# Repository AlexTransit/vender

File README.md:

# What
Vender is free open source VMC (Vending Machine Controller). (fork https://github.com/temoto/vender)
This software has been working since 2019 (small network of coffee machines.)
equipment used:
VMC: eVend8 (bill validators: JCM300 and ICT7, Coin validators: CoinCo Global2 and Coges Aeterna)
Main Board: OrangePi Lite, 
additional display: 320x240 controller st7789v 
additional sound card: noname USB sound card

Status:
- MDB adapter hardware module - works
- VMC - works

# Hardware

Required for VMC:
- Works on RaspberryPI, OrangePi Lite (H3) OrangePi PC2(H5). Possibly anything with GPIO that runs Go/Linux.
- MDB signal current limiter - required, see files in `hardware/schematic` (https://namanow.org/wp-content/uploads/Multi-Drop-Bus-and-Internal-Communication-Protocol.pdf)
- MDB adapter, takes care of 9bit and timing, we use ATMega328p (168) with `hardware/mega-firmware`. 
    (software option is available: https://github.com/temoto/iodin . in a similar solution, another author made measurements. delay may be up to 10ms. in the specification MDB the maximum delay is 5ms )

Supported peripherals:
- MDB coin acceptor, bill validator
- Evend MDB drink devices
- any MDB device via configuration scenarios (work in progress)
- MT16S2R HD44780-like text display
- TWI(I2C) numpad keyboard
- graphic display (anyone registered in the system.)

# Design

VMC overall structure:
- engine (see internal/engine packages) executes actions, handles concurrency and errors
- device/feature drivers provide actions to engine
- configuration scenario specifies action groups and when to execute them

# Build

- Install latest Go from https://golang.org/dl/ (now worked on 1.24)
- Set target environment, default is `GOARCH=arm GOOS=linux`
- Run `script/build`
- Deploy file `build/vender` to your hardware

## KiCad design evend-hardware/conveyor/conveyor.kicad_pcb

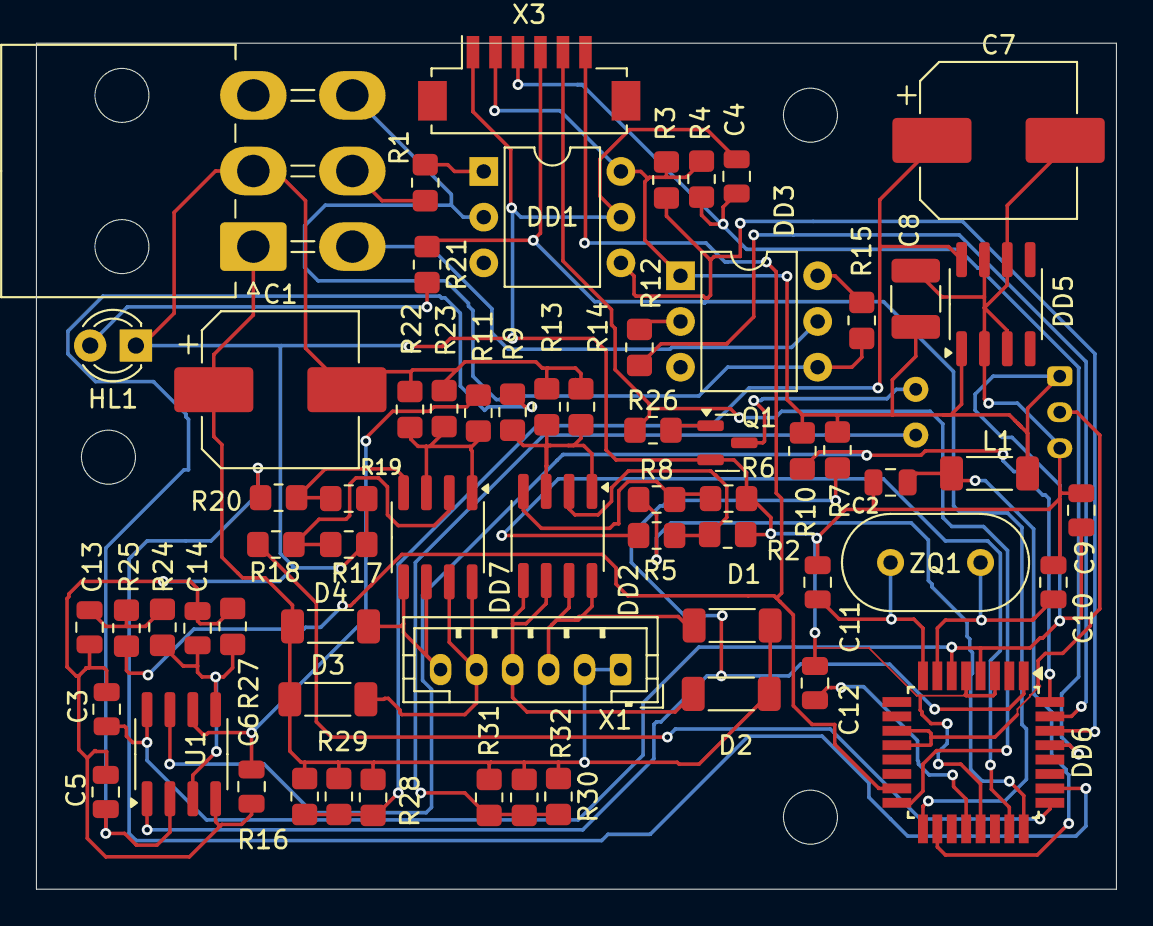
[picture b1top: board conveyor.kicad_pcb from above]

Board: 2 copper layers, 60.0 x 47.0 mm, 65 parts (1 on the bottom side), 45 nets.

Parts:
C1, C7: 100 35v; CP_Elec_8x10.5
C2, C3, C4, C5, C6, C9, C10, C11, C12, C13, C14: C; C_0805_2012Metric
C8: TAN; C_1210_3225Metric_Pad1.33x2.70mm_HandSolder
D1, D2, D3, D4: 10BQ060; L_1806_4516Metric
DD1: H11L1; DIP-6_W7.62mm
DD2, DD7: F7341; SOIC-8_3.9x4.9mm_P1.27mm
DD3: 4N37; DIP-6_W7.62mm
DD5: L78L05_SO8; SOIC-8_3.9x4.9mm_P1.27mm
DD6: ATmega8-16A; TQFP-32_7x7mm_P0.8mm
HL1: LED; LED_D3.0mm
L1: L; L_1806_4516Metric
Q1: Q_NPN_BEC; SOT-23
R1: 152; R_0805_2012Metric_Pad1.20x1.40mm_HandSolder
R2, R6, R17, R19, R25: 513; R_0805_2012Metric_Pad1.20x1.40mm_HandSolder
R3, R7, R10, R26, R30, R31, R32: 472; R_0805_2012Metric_Pad1.20x1.40mm_HandSolder
R4, R9, R11, R27: 103; R_0805_2012Metric_Pad1.20x1.40mm_HandSolder
R5, R8, R12, R18, R20: 181; R_0805_2012Metric_Pad1.20x1.40mm_HandSolder
R13, R14, R22, R23: 1; R_0805_2012Metric_Pad1.20x1.40mm_HandSolder
R15: 104; R_0805_2012Metric_Pad1.20x1.40mm_HandSolder
R16, R28, R29: 122; R_0805_2012Metric_Pad1.20x1.40mm_HandSolder
R21: 102; R_0805_2012Metric_Pad1.20x1.40mm_HandSolder
R24: 363; R_0805_2012Metric_Pad1.20x1.40mm_HandSolder
U1: LM393; SOIC-8_3.9x4.9mm_P1.27mm
US1: LG206D; Kodenshi_LG206D
X1: Conn_01x06; JST_PH_B6B-PH-K_1x06_P2.00mm_Vertical
X2: MDB; Molex_Mini-Fit_Jr_5569-06A2_2x03_P4.20mm_Horizontal
X3: Conn_01x06; Hirose_DF13C_CL535-0406-3-51_1x06-1MP_P1.25mm_Vertical
ZQ1: 7.3728; Resonator-2Pin_W10.0mm_H5.0mm

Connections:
+5V: C3.2, C8.1, C9.2, DD1.6, DD3.1, DD5.1 (OUT), DD6.4 (VCC), DD6.6 (VCC), L1.1, R3.1, R4.2, R7.1, R10.1, U1.8 (V+), US1.1 (VCC), X3.2
+24V: C1.1, D1.1 (K), D2.1 (K), D3.1 (K), D4.1 (K), R16.1, R28.1, R29.1, R30.1, R31.1, R32.1, X1.1, X1.2, X2.1
GND: C1.2, C2.1, C3.1, C4.2, C5.1, C6.1, C7.2, C8.2, C9.1, C10.1, C11.1, C12.1, C13.1, C14.1, DD1.5, DD5.2 (GND), DD5.3 (GND), DD5.6 (GND), DD5.7 (GND), DD6.3 (GND), DD6.5 (GND), DD6.21 (AGND), HL1.1 (K), Q1.2 (E), R2.2, R6.2, R13.2, R14.2, R17.2, R19.2, R22.2, R23.2, R27.1, U1.4 (V-), US1.3 (GND), X2.2, X3.1
GNDS: DD1.2, DD3.4, R15.1, X2.6
unnamed: C13.2, R24.1, R25.2
unnamed: DD1.1, R1.2
unnamed: DD2.2 (G), R2.1, R5.2
unnamed: DD2.1 (S), DD2.3 (1), R9.1, R13.1, R14.1
unnamed: DD2.4 (G), R6.1, R8.2
unnamed: DD3.2, R12.2
unnamed: DD3.6, R15.2
unnamed: C7.1, DD5.8 (IN), R16.2, R28.2, R29.2
unnamed: C12.2, DD6.20 (AREF)
unnamed: C2.2, DD6.18 (AVCC), L1.2
unnamed: C10.2, DD6.7 (PB6/XTAL1), ZQ1.1
unnamed: C11.2, DD6.8 (PB7/XTAL2), ZQ1.2
unnamed: DD7.2 (G), R17.1, R18.2
unnamed: DD7.1 (S), DD7.3 (1), R11.1, R22.1, R23.1
unnamed: DD7.4 (G), R19.1, R20.2
unnamed: HL1.2 (A), R21.2
unnamed: Q1.1 (B), R26.2
unnamed: Q1.3 (C), US1.5 (K)
unnamed: C14.2, R25.1, R27.2, U1.3 (+), U1.5 (+)
unnamed: C5.2, R9.2, U1.2 (-)
unnamed: C6.2, R11.2, U1.6 (-)
unnamed: R30.2, R31.2, R32.2, US1.4 (A)
unnamed: DD3.5, X2.4
unnamed: R1.1, X2.5
RX: DD1.4, DD6.30 (PD0), R3.2
TX: DD6.31 (PD1), R12.1
c-w11: DD6.23 (PC0), R5.1
c-w12: DD6.24 (PC1), R8.1
c-w21: DD6.25 (PC2), R18.1
c-w22: DD6.26 (PC3), R20.1
cc1: DD6.1 (PD3), R7.2, U1.1
cc2: DD6.32 (PD2), R10.2, U1.7
encoder: DD6.11 (PD7), DD6.12 (PB0), US1.2 (VOUT)
miso: DD6.16 (PB4), R26.1, X3.5
mosi: DD6.15 (PB3), R24.2, X3.6
reset: C4.1, DD6.29 (PC6/~RESET), R4.1, X3.3
sck: DD6.17 (PB5), R21.1, X3.4
winding1-1: D1.2 (A), DD2.7 (D), DD2.8 (D), X1.3
winding1-2: D2.2 (A), DD2.5 (D), DD2.6 (D), X1.4
winding2-1: D3.2 (A), DD7.7 (D), DD7.8 (D), X1.5
winding2-2: D4.2 (A), DD7.5 (D), DD7.6 (D), X1.6

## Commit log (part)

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2024-02-07 add device error code
2024-02-07 elevator rewirite
2024-02-09 config rewrite
2024-02-10 override structure. add function
2024-02-10 add config hardware override
2024-02-13 upgrade go 1.22
2024-02-24 dev set errorcode proto2
2024-02-24 espresso grind restart
2024-02-25 mon. remove gift? change dispence
2024-02-25 modify coin dispense
2024-02-26 fix coges bug. (diagnostics return )
2024-03-02 -- fix warning
2024-03-02 coin. add return and status
2024-03-02 sound volume fix
2024-03-04 wd disabled fix
2024-03-04 esspresso grind 5 times
2024-03-12 espresso grind
2024-03-12 valve remove hot validate
2024-03-12 valve
2024-04-12 mix err
2024-05-02 tune key
2024-05-14 change valve timeout pool
2024-05-14 fix water run timeout
2024-06-09 change input init
2024-06-10 set arg as interface
2024-06-10 added text in scenario
2024-06-10 added sound play in scenario
2024-07-27 added autosync atribute on inventoryf ile
2024-07-30 set atribute via unix package
2024-10-23 add conveyor plate shematic
2024-11-15 inventory. changing file handling
2024-12-06 fix. qr cancel
2024-12-07 upgrade protobuf lib
2024-12-07 upgrade protobuff
2024-12-08 add payer order amount in show qr proto
2024-12-08 переделал commang.go
2024-12-08 fix 2 bugs
2024-12-09 automatically sets the service button
2024-12-10 add check menu and --
2024-12-10 fix. restore stty after engine-cli
2024-12-21 отделил меню
2024-12-28 default config
2025-01-12 auto level-value in service
2025-01-13 broken file to config
2025-01-15 upgrade go 1,23.4
2025-01-16 auto reporter
2025-01-16 end work state
2025-01-17 fix QR amount
2025-01-20 calc cost
2025-01-20 fix text lines (qr)
2025-01-20 fix deprecated
2025-01-20 fix. remove test string
2025-01-20 fix bug
2025-01-21 espresso. grind func for stok
2025-01-21 stop money pull if money abort/
2025-01-29 show coins when loading
2025-03-30 fix bill stop
2025-03-31 fix bill escrow
2025-04-02 fix bill stop. reject escow
2025-04-05 set coplete order if dirty 0
2025-04-16 mixer add restart if shake
2025-04-17 uggrade sound add tts
2025-05-18 update conveyor schematic
2025-05-28 optimize structs
2025-05-31 dispence max amount if count =
2025-05-31 Revert "optimize structs"
    This reverts commit dccf9ed9d7241209e4a64344aeacbecc6a1394d0.
2025-06-08 bill bancnote limit
2025-07-10 upgrade mqtt
2025-07-10 fix mqtt panic
2025-07-11 fix mix timiout error
2025-08-16 remove unused
2025-08-17 fix nil doer on remote cook
2025-08-17 fix fix
2025-09-04 show mix gopp action
2025-09-07 fix syntax
2025-10-11 fix make tuned selected cook
2025-10-16 set custom charmap
2025-10-16 страницы знакогенераторов на экранах 1602 уже не используются.
2026-02-07 update mqtt
2026-02-07 add makefile
2026-02-10 fix sound
2026-02-10 update sound lib
2026-02-12 update makefile and settings
2026-02-12 fix makefile
2026-02-20 update tele (add webuser
2026-03-03 update make
2026-03-06 remote cook. check overdraft
2026-03-19 ai fix1
2026-03-19 ai fix2
2026-03-21 fix config
2026-03-21 fix text display
2026-03-21 fix input
2026-03-21 fix inventory
2026-03-21 fix state
2026-03-26 change default tmp folder
2026-03-26 sound fix
2026-04-20 add error actions
2026-04-20 add docs and create default config
2026-04-21 fix doer nill o nremote cook
2026-04-23 update valve
2026-04-28 upgrade go 1.26
2026-04-29 conv fix
2026-05-02 add dummy mdb and text display driver.
2026-05-03 add error scenario
2026-05-04 change input func
2026-05-04 add key press ok event in scenario
2026-05-04 disable keyboard before cooking
2026-05-04 restore input
2026-05-11 add err-11 on proto2 (timeout)
2026-05-11 conv set timeout 20
